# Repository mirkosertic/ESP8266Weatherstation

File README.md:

# ESP8266 Climate Sensor

This project provides an ESP8266 based climate sensor with the following features:

* MQTT status reporting / remote control
* Home Assistant integration with device autodiscovery
* Multi-Sensor display indoor/outdoor with Weather forecast
* Battery powered with deep sleep support

## Supported hardware

* ESP8266 Lolin D1 Mini with Deep-Sleep
* BME280 climate sensor (i2c-Mode)
* 200x200 WeAct EPD/eInk display (4-Wire SPI)

## Display & HA integration

Weather data is presented the following way using the eInk-Display:

The following sensors are automatically discovered by the HA MQTT auto discovery:

The device collects the following data points:

- Absolute humidity (calculated)
- Relative humidity
- Current battery voltage
- Air pressure
- Temperature
- Overall cycle time of the sensor for one measurement
- Wifi quality

## Schematics & Prototype

The KiCad 8.0 project is located in the kicad folder.

Here is the wiring schematic drawing:

## Manual

TBD

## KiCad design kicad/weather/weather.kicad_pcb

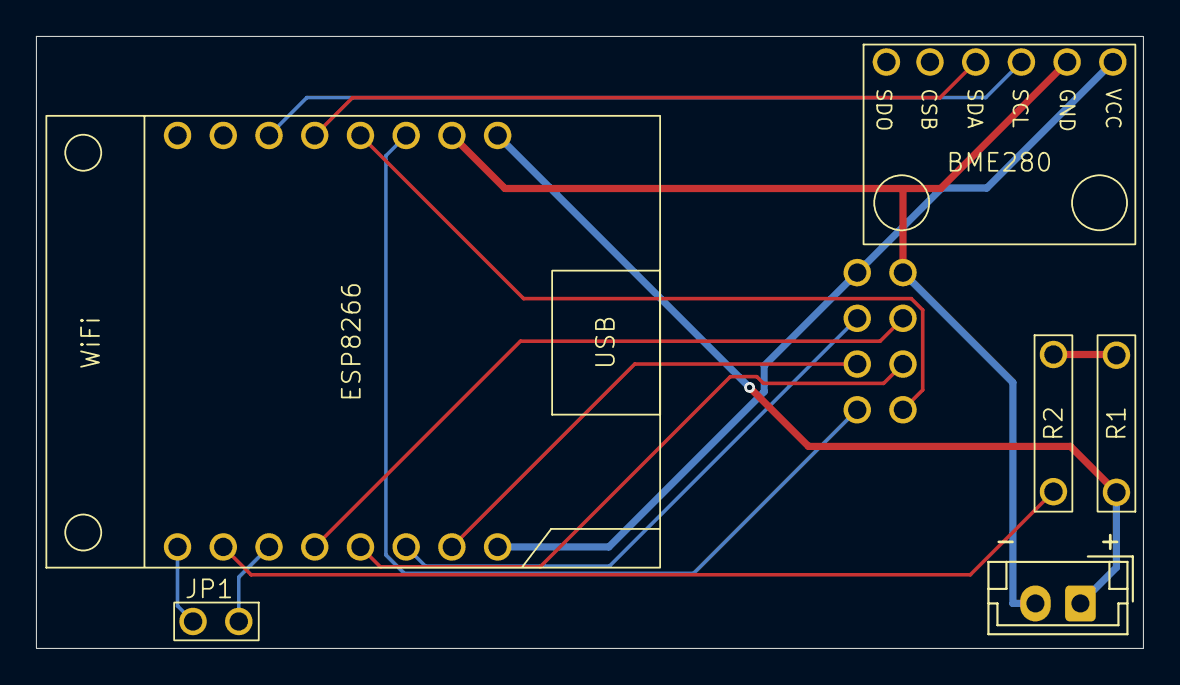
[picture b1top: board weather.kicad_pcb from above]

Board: 2 copper layers, 61.5 x 34.0 mm, 7 parts (1 on the bottom side), 15 nets.

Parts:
-      +: 3.7V; JST_EH_B2B-EH-A_1x02_P2.50mm_Vertical
BME280: BME280 DIP
ESP8266: LOLIN D1 MINI DIP
JP1: Deep sleep / Programmimg; 2er DIP
R1, R2: 200K; 4er DIP
WeAct154EPD1: 1,54 EPD SPI DIP

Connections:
3V3: BME280.1 (VCC), ESP8266.9 (3V3), WeAct154EPD1.8 (VCC)
/A0: ESP8266.15 (A0), R2.2
/BME_I2C_SCL: BME280.3 (SCL), ESP8266.3 (D1)
/BME_I2C_SDA: BME280.4 (SDA), ESP8266.4 (D2)
/D0: ESP8266.14 (D0), JP1.1 (A)
/DIS_BUSY: ESP8266.5 (D3), WeAct154EPD1.1 (BUSY)
/DIS_CS: ESP8266.10 (D8), WeAct154EPD1.4 (CS)
/DIS_DC: ESP8266.12 (D6), WeAct154EPD1.3 (DC)
/DIS_RST: ESP8266.6 (D4), WeAct154EPD1.2 (RST)
/DIS_SCL: ESP8266.13 (D5), WeAct154EPD1.5 (SCL)
/DIS_SDA: ESP8266.11 (D7), WeAct154EPD1.6 (SDA)
/RST: ESP8266.16 (RST), JP1.2 (B)
BAT: - +.1 (+), ESP8266.8 (VBUS), R1.1
GND: - +.2 (-), BME280.2 (GND), ESP8266.7 (GND), WeAct154EPD1.7 (GND)
unnamed: R1.2, R2.1

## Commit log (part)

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2024-09-20 Updated to HQ MQTT Autodiscovery
2024-10-01 Added firmware version and RSSI reporting
2024-10-10 Bug fixing and eInk-Display
2024-10-10 Added build badge
2024-10-11 Added home assistant sensor statistics
2024-10-11 Working on display icons and local time
2024-10-16 Added some documentation
2024-10-20 Finalized schematics and PCB
2024-10-23 Minor changes on schematics
2024-10-27 Updated documentation
2024-10-30 Documentation & KiCad update
2024-11-01 Added switch for hw w/o display
2024-11-01 Added more documentation
2024-11-04 Tests with different sampling rates
2025-03-09 Working on display refresh performance
2026-04-17 Added pull request workflow
